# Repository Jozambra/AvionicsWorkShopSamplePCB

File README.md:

# AvionicsWorkShopSamplePCB
This repo contains the design files for the sample PCB used for the avionics Workshop between Arbalest Rocketry and Astra Labs.

This project was developed in KiCAD 10.0; it requires a similar or newer version to be propely opened. 

The dependencies folder includes the libraries used in this PCB; they might need to be manually imported if shortcut addresses become non-funcitonal of if any directory name is changed.

This project is a bare-minimun design that will likely require non-trivial modifications to match the avionics requirements of a given mission; treat this file as a base from which to build up
your own design.

Originated by: JZ
Date: Nov 21, 2026

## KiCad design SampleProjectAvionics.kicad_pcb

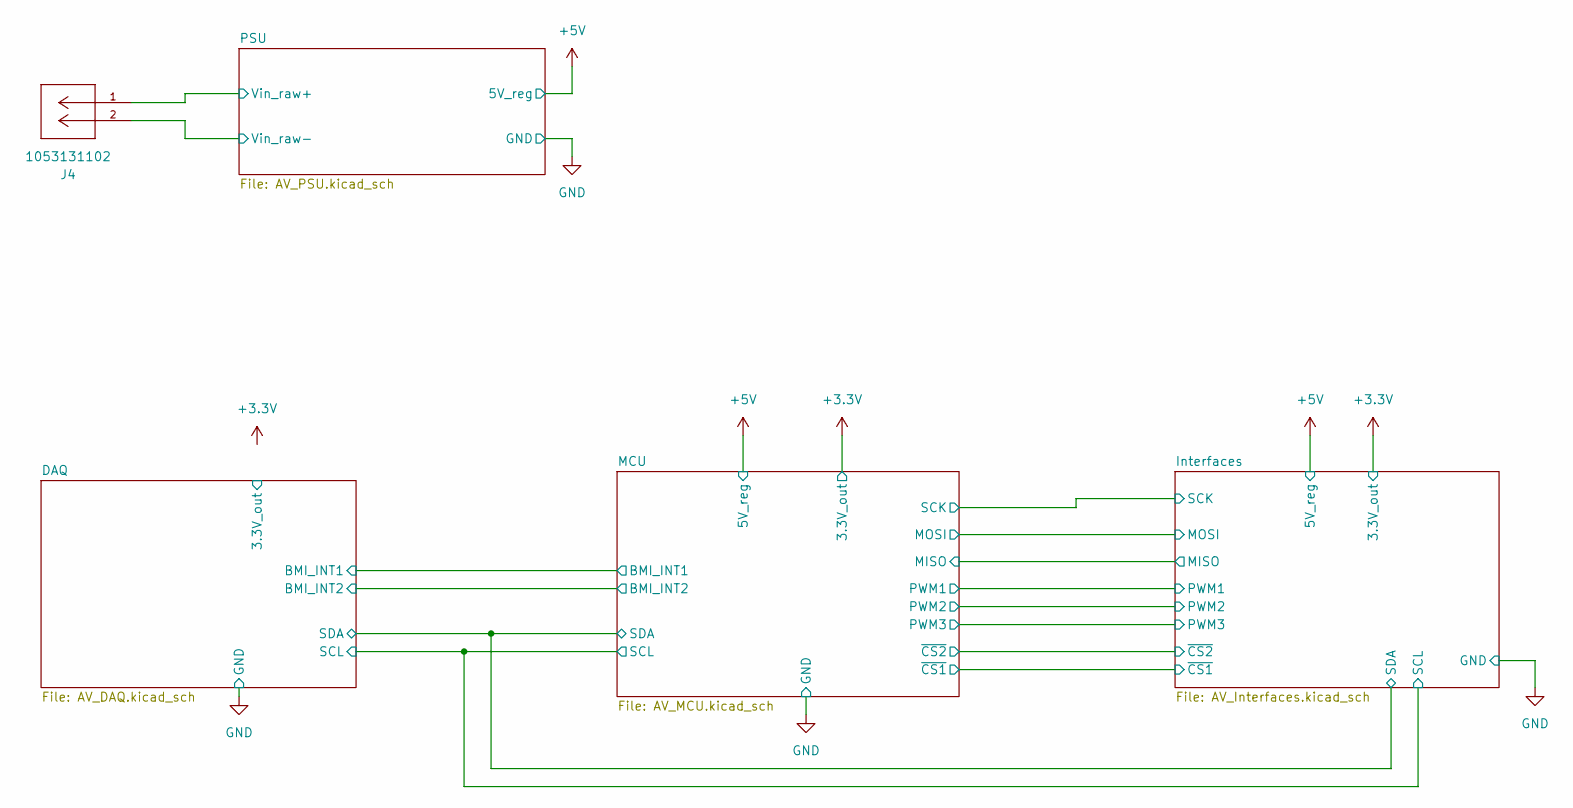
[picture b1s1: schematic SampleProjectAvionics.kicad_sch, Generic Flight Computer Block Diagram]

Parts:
J4: 1053131102; CONN_SD-105313-100_02_MOL; MPN 1053131102

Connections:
Vin_raw+: J4.1; also elsewhere on the board
Vin_raw-: J4.2; also elsewhere on the board

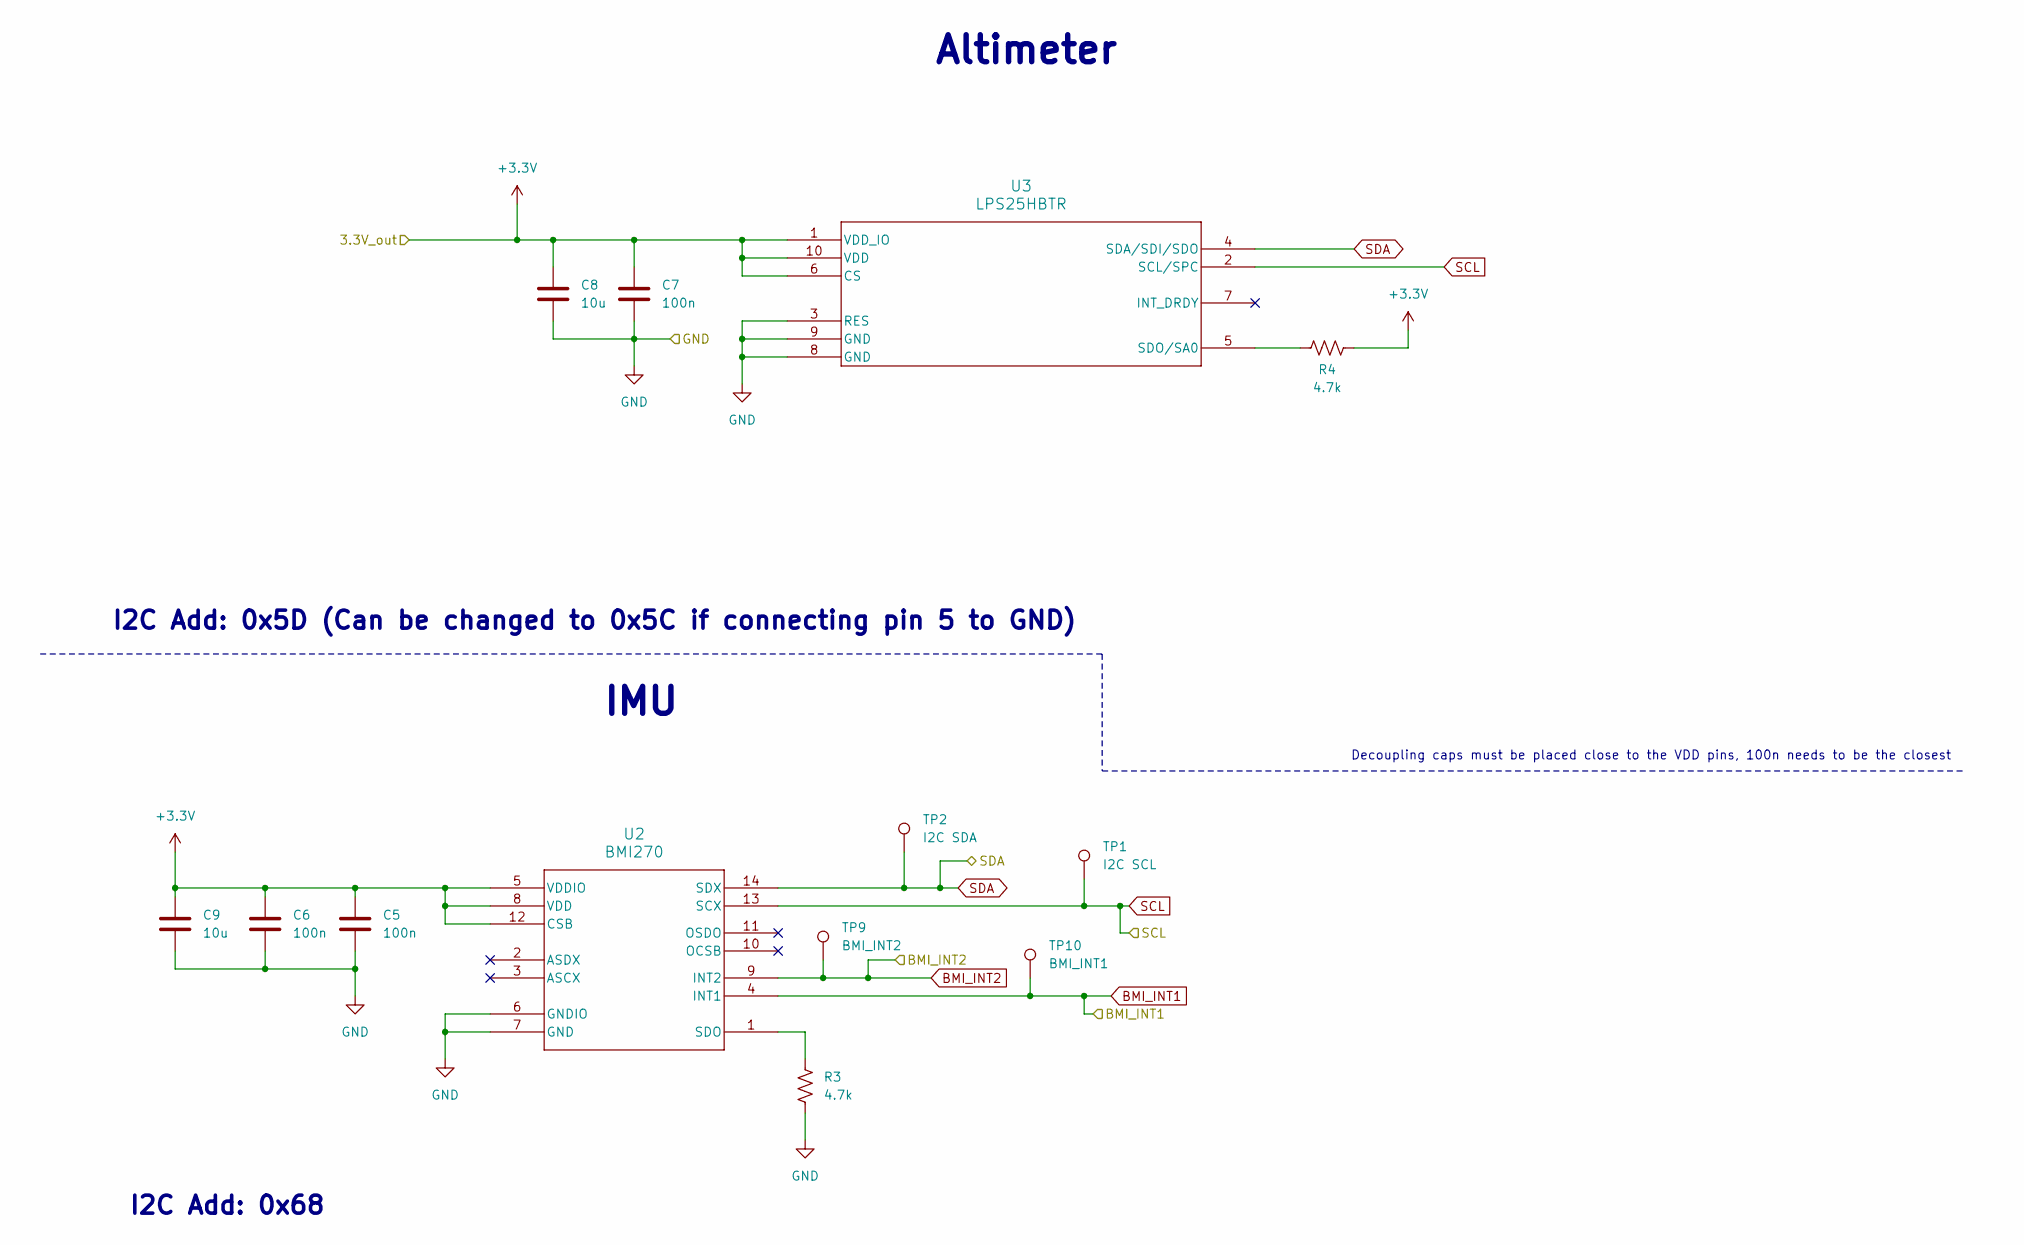
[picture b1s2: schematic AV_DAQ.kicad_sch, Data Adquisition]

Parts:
C5, C6, C7: 100n; C_0805_2012Metric_Pad1.18x1.45mm_HandSolder
C8, C9: 10u; C_0805_2012Metric_Pad1.18x1.45mm_HandSolder
R3, R4: 4.7k; R_0805_2012Metric_Pad1.20x1.40mm_HandSolder
TP1: I2C SCL; TestPoint_Keystone_5019_Miniature
TP2: I2C SDA; TestPoint_Keystone_5019_Miniature
TP9: BMI_INT2; TestPoint_Keystone_5019_Miniature
TP10: BMI_INT1; TestPoint_Keystone_5019_Miniature
U2: BMI270; BMI270_BOS-M
U3: LPS25HBTR; HLGA10_2P5X2P5_STM

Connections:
+3.3V: C5.1, C6.1, C7.1, C8.1, C9.1, R4.1, U2.5 (VDDIO), U2.8 (VDD), U2.12 (CSB), U3.1 (VDD_IO), U3.6 (CS), U3.10 (VDD); also elsewhere on the board
BMI_INT1: TP10.1 (1_1), U2.4 (INT1); also elsewhere on the board
BMI_INT2: TP9.1 (1_1), U2.9 (INT2); also elsewhere on the board
unnamed: R3.2, U2.1 (SDO)
unnamed: R4.2, U3.5 (SDO/SA0)
SCL: TP1.1 (1_1), U2.13 (SCX), U3.2 (SCL/SPC); also elsewhere on the board
SDA: TP2.1 (1_1), U2.14 (SDX), U3.4 (SDA/SDI/SDO); also elsewhere on the board
Vin_raw-: C5.2, C6.2, C7.2, C8.2, C9.2, R3.1, U2.6 (GNDIO), U2.7 (GND), U3.3 (RES), U3.8 (GND), U3.9 (GND); also elsewhere on the board

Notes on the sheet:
Decoupling caps must be placed close to the VDD pins, 100n needs to be the closest
IMU
I2C Add: 0x5D (Can be changed to 0x5C if connecting pin 5 to GND)
I2C Add: 0x68
Altimeter

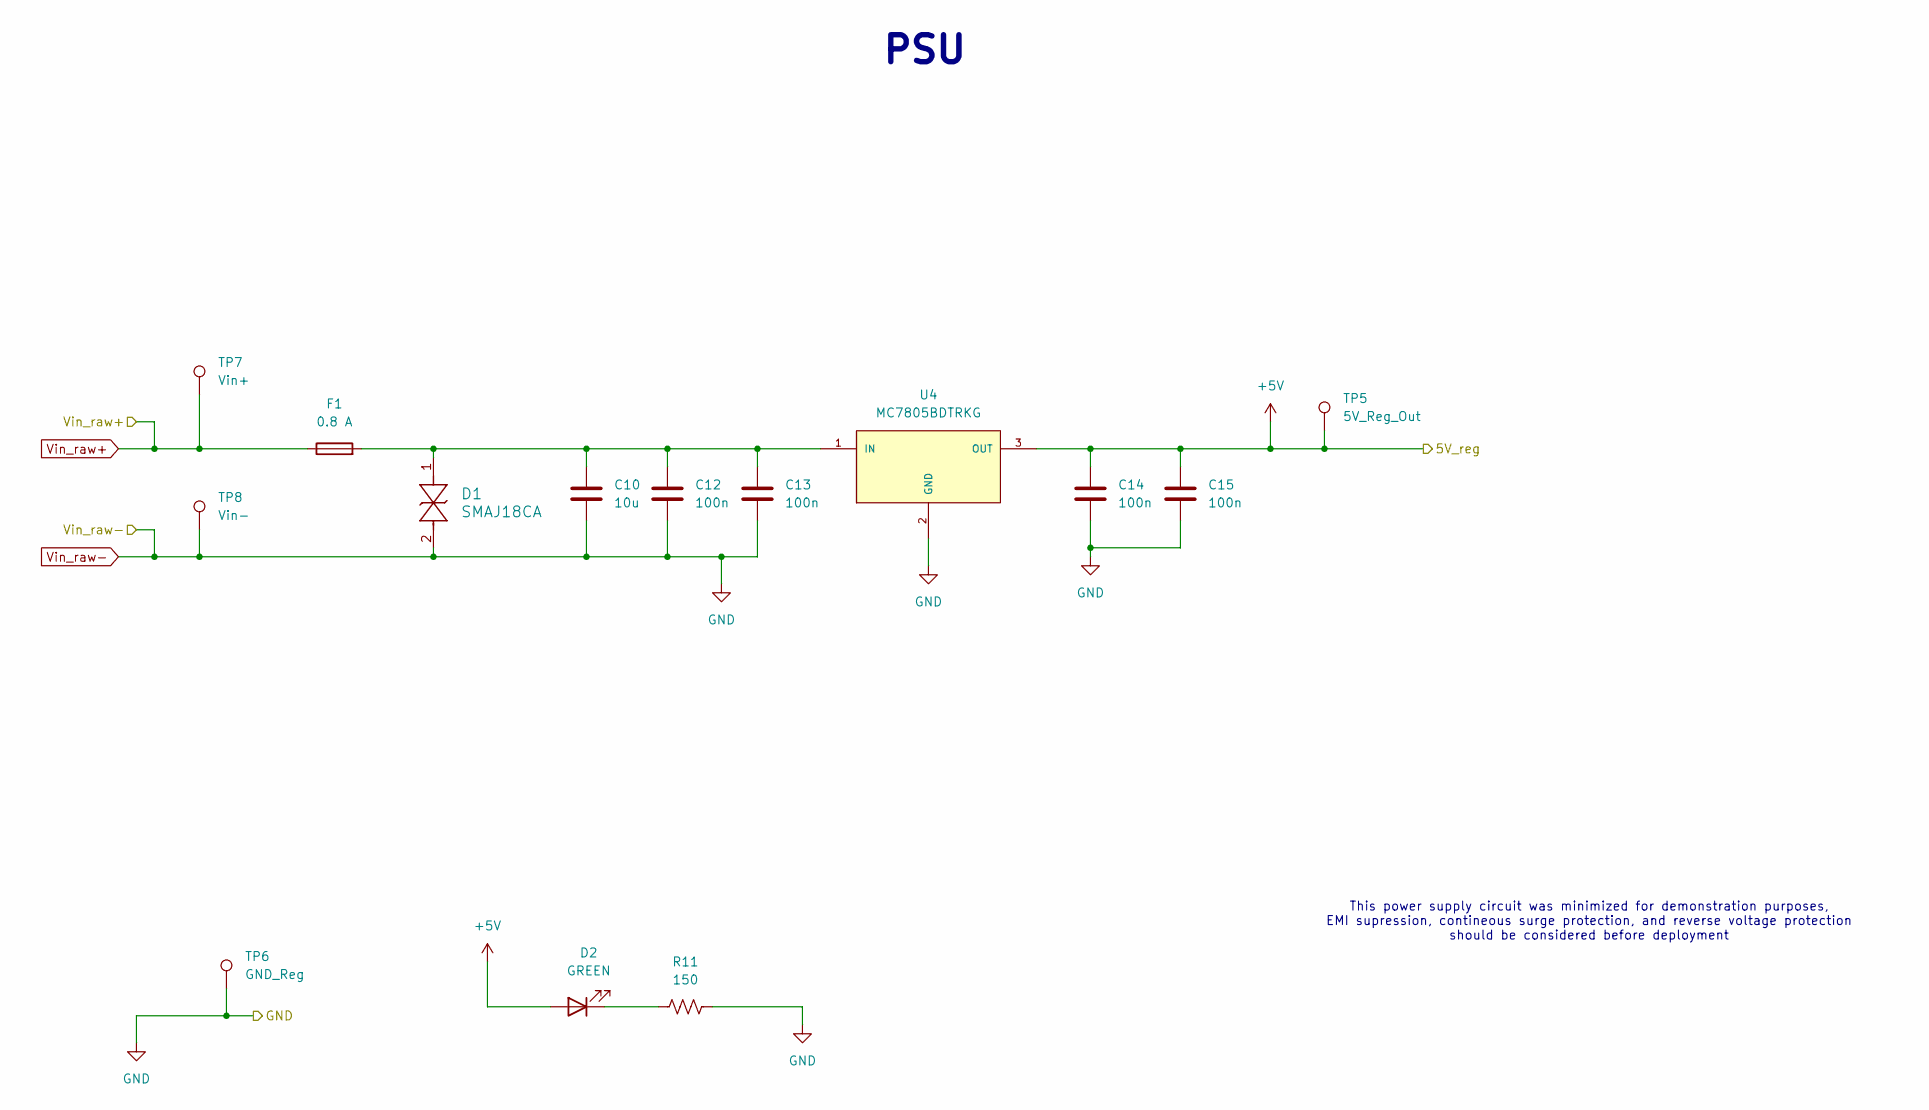
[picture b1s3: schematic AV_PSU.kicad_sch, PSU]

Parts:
C10: 10u; C_0805_2012Metric_Pad1.18x1.45mm_HandSolder
C12, C13, C14, C15: 100n; C_0805_2012Metric_Pad1.18x1.45mm_HandSolder
D1: SMAJ18CA; SMASeries_LTF
D2: GREEN; LED_0805_2012Metric_Pad1.15x1.40mm_HandSolder
F1: 0.8 A; Fuse_1206_3216Metric_Pad1.42x1.75mm_HandSolder
R11: 150; R_0805_2012Metric_Pad1.20x1.40mm_HandSolder
TP5: 5V_Reg_Out; TestPoint_Keystone_5019_Miniature
TP6: GND_Reg; TestPoint_Keystone_5019_Miniature
TP7: Vin+; TestPoint_Keystone_5019_Miniature
TP8: Vin-; TestPoint_Keystone_5019_Miniature
U4: MC7805BDTRKG; DPAK229P990X238-4N; PARTREV 27

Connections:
+5V: C14.1, C15.1, D2.2 (A), TP5.1 (1_1), U4.3 (OUT); also elsewhere on the board
unnamed: D2.1 (K), R11.1
unnamed: C10.1, C12.1, C13.1, D1.1, F1.2, U4.1 (IN)
Vin_raw+: F1.1, TP7.1 (1_1); also elsewhere on the board
Vin_raw-: C10.2, C12.2, C13.2, C14.2, C15.2, D1.2, R11.2, TP6.1 (1_1), TP8.1 (1_1), U4.2 (GND); also elsewhere on the board

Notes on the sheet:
This power supply circuit was minimized for demonstration purposes, EMI supression, contineous surge protection, and reverse voltage protection should be considered before deployment
PSU

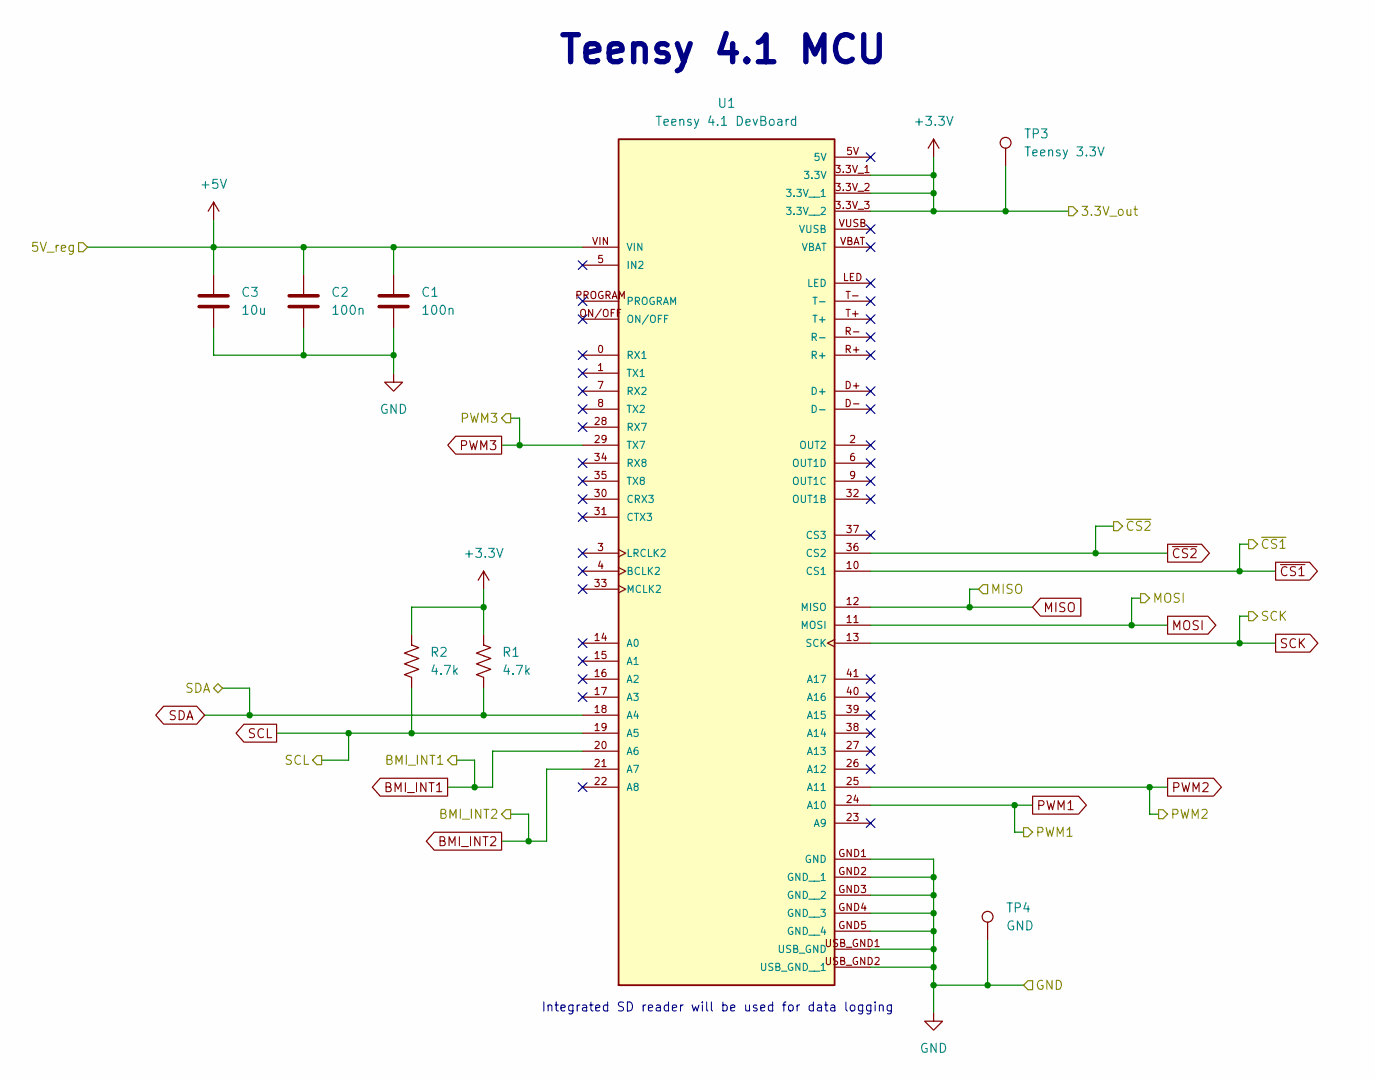
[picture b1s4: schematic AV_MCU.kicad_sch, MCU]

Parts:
C1, C2: 100n; C_0805_2012Metric_Pad1.18x1.45mm_HandSolder
C3: 10u; C_0805_2012Metric_Pad1.18x1.45mm_HandSolder
R1, R2: 4.7k; R_0805_2012Metric_Pad1.20x1.40mm_HandSolder
TP3: Teensy 3.3V; TestPoint_Keystone_5019_Miniature
TP4: GND; TestPoint_Keystone_5019_Miniature
U1: Teensy 4.1 DevBoard; MODULE_DEV-16771; MPN DEV-16771

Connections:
+3.3V: R1.1, R2.1, TP3.1 (1_1), U1.3.3V_1 (3.3V), U1.3.3V_2 (3.3V__1), U1.3.3V_3 (3.3V__2); also elsewhere on the board
+5V: C1.1, C2.1, C3.1, U1.VIN; also elsewhere on the board
BMI_INT1: U1.20 (A6); also elsewhere on the board
BMI_INT2: U1.21 (A7); also elsewhere on the board
MISO: U1.12 (MISO); also elsewhere on the board
MOSI: U1.11 (MOSI); also elsewhere on the board
PWM1: U1.24 (A10); also elsewhere on the board
PWM2: U1.25 (A11); also elsewhere on the board
PWM3: U1.29 (TX7); also elsewhere on the board
SCK: U1.13 (SCK); also elsewhere on the board
SCL: R2.2, U1.19 (A5); also elsewhere on the board
SDA: R1.2, U1.18 (A4); also elsewhere on the board
Vin_raw-: C1.2, C2.2, C3.2, TP4.1 (1_1), U1.GND1 (GND), U1.GND2 (GND__1), U1.GND3 (GND__2), U1.GND4 (GND__3), U1.GND5 (GND__4), U1.USB_GND1 (USB_GND), U1.USB_GND2 (USB_GND__1); also elsewhere on the board
~CS1: U1.10 (CS1); also elsewhere on the board
~CS2: U1.36 (CS2); also elsewhere on the board

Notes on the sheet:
Integrated SD reader will be used for data logging
Teensy 4.1 MCU

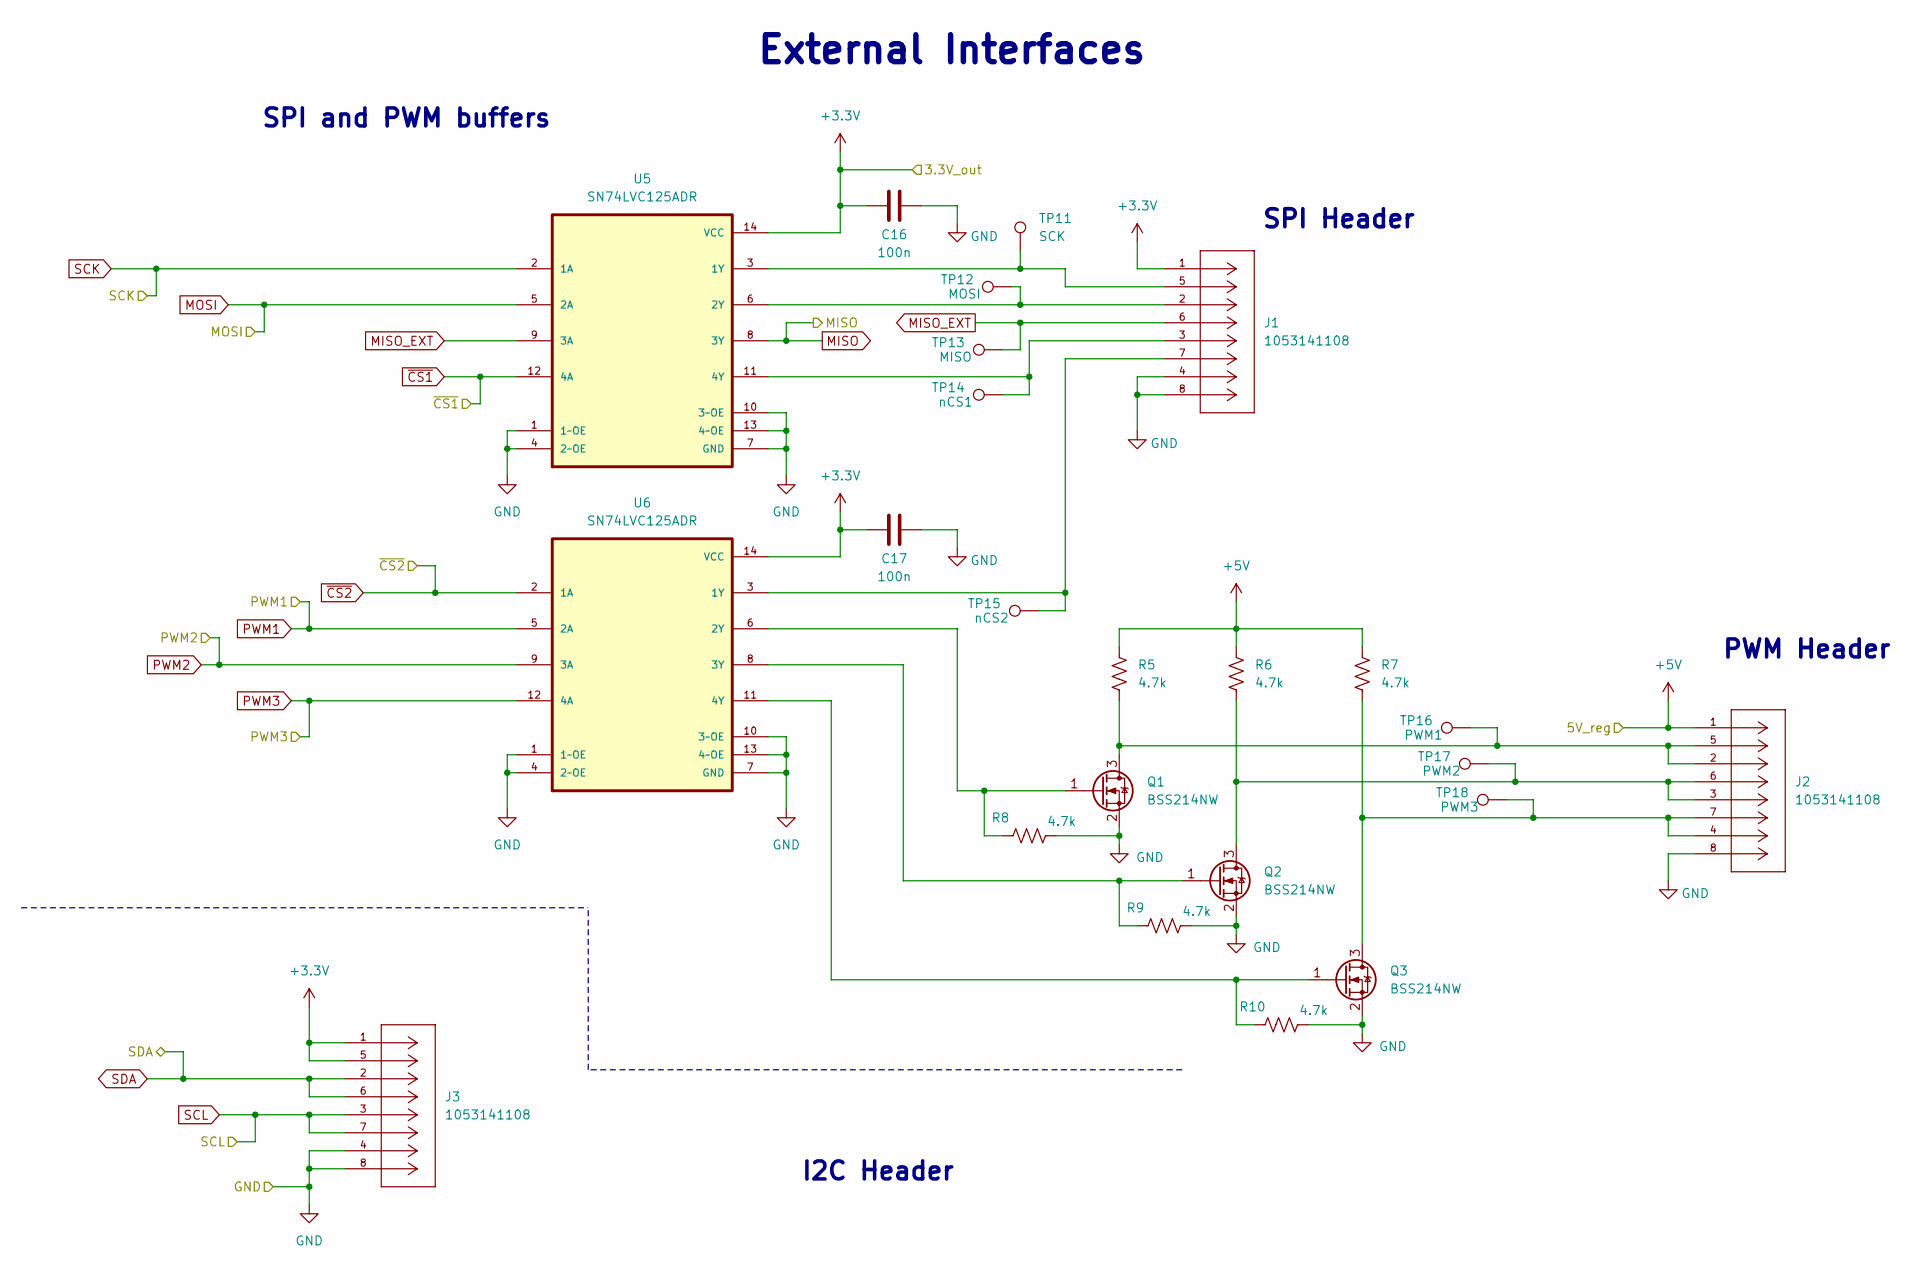
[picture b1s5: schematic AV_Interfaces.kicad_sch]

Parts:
C16, C17: 100n; C_0805_2012Metric_Pad1.18x1.45mm_HandSolder
J1, J2, J3: 1053141108; CONN_SD-105314-100_08_MOL; MPN 1053141108
Q1, Q2, Q3: BSS214NW; SOT-323_SC-70
R5, R6, R7, R8, R9, R10: 4.7k; R_0805_2012Metric_Pad1.20x1.40mm_HandSolder
TP11: SCK; TestPoint_Keystone_5019_Miniature
TP12: MOSI; TestPoint_Keystone_5019_Miniature
TP13: MISO; TestPoint_Keystone_5019_Miniature
TP14: nCS1; TestPoint_Keystone_5019_Miniature
TP15: nCS2; TestPoint_Keystone_5019_Miniature
TP16: PWM1; TestPoint_Keystone_5019_Miniature
TP17: PWM2; TestPoint_Keystone_5019_Miniature
TP18: PWM3; TestPoint_Keystone_5019_Miniature
U5, U6: SN74LVC125ADR; SOIC127P600X175-14N; MPN SN74LVC125ADR

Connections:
+3.3V: C16.1, C17.1, J1.1, J3.1, J3.5, U5.14 (VCC), U6.14 (VCC); also elsewhere on the board
+5V: J2.1, R5.1, R6.1, R7.1; also elsewhere on the board
MISO: U5.8 (3Y); also elsewhere on the board
MISO_EXT: J1.6, TP13.1 (1_1), U5.9 (3A)
MOSI: U5.5 (2A); also elsewhere on the board
unnamed: J2.2, J2.5, Q1.3 (D), R5.2, TP16.1 (1_1)
unnamed: Q1.1 (G), R8.1, U6.6 (2Y)
unnamed: J2.3, J2.6, Q2.3 (D), R6.2, TP17.1 (1_1)
unnamed: Q2.1 (G), R9.1, U6.8 (3Y)
unnamed: J2.4, J2.7, Q3.3 (D), R7.2, TP18.1 (1_1)
unnamed: Q3.1 (G), R10.1, U6.11 (4Y)
unnamed: J1.5, TP11.1 (1_1), U5.3 (1Y)
unnamed: J1.2, TP12.1 (1_1), U5.6 (2Y)
unnamed: J1.3, TP14.1 (1_1), U5.11 (4Y)
unnamed: J1.7, TP15.1 (1_1), U6.3 (1Y)
PWM1: U6.5 (2A); also elsewhere on the board
PWM2: U6.9 (3A); also elsewhere on the board
PWM3: U6.12 (4A); also elsewhere on the board
SCK: U5.2 (1A); also elsewhere on the board
SCL: J3.3, J3.7; also elsewhere on the board
SDA: J3.2, J3.6; also elsewhere on the board
Vin_raw-: C16.2, C17.2, J1.4, J1.8, J2.8, J3.4, J3.8, Q1.2 (S), Q2.2 (S), Q3.2 (S), R8.2, R9.2, R10.2, U5.1 (1~OE), U5.4 (2~OE), U5.7 (GND), U5.10 (3~OE), U5.13 (4~OE), U6.1 (1~OE), U6.4 (2~OE), U6.7 (GND), U6.10 (3~OE), U6.13 (4~OE); also elsewhere on the board
~CS1: U5.12 (4A); also elsewhere on the board
~CS2: U6.2 (1A); also elsewhere on the board

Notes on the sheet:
SPI Header
PWM Header
External Interfaces
I2C Header
SPI and PWM buffers

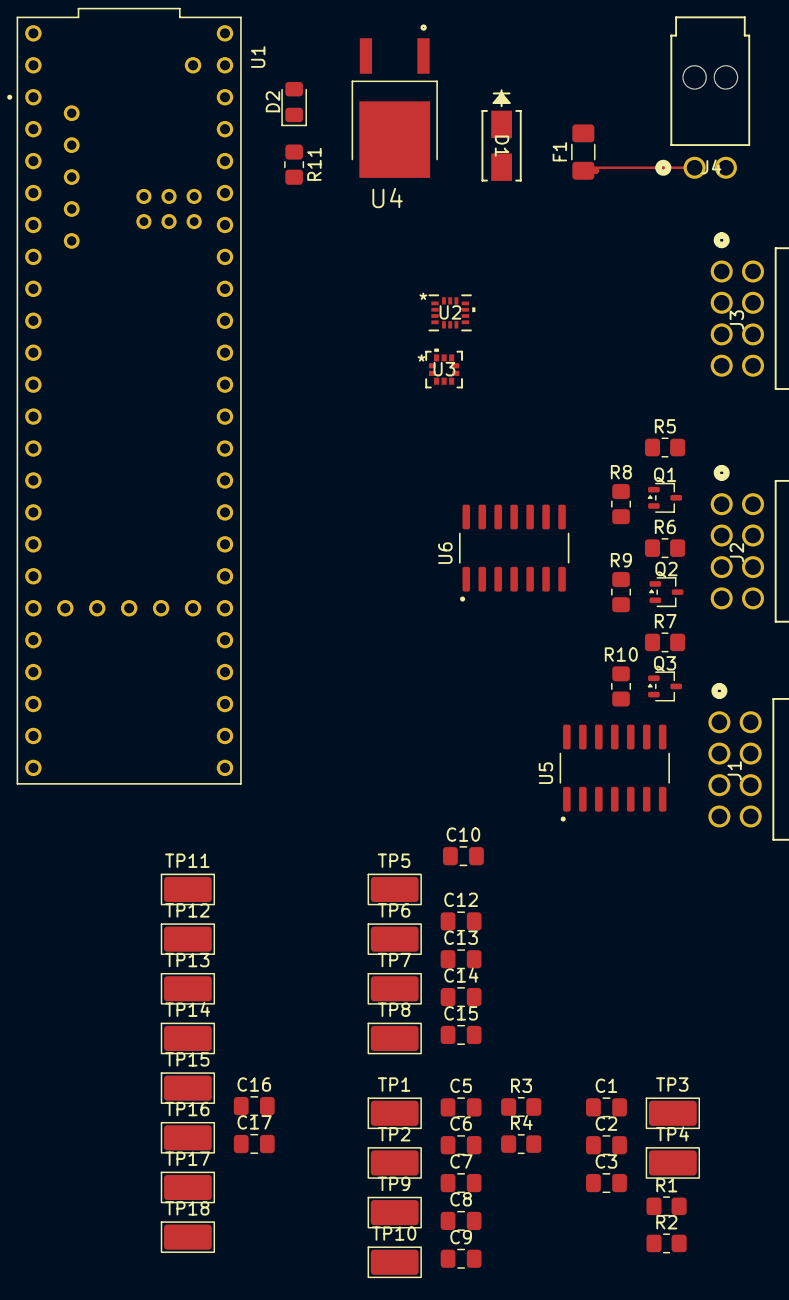
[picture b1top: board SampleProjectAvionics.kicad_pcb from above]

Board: 2 copper layers, 60 parts (0 on the bottom side), 31 nets.
